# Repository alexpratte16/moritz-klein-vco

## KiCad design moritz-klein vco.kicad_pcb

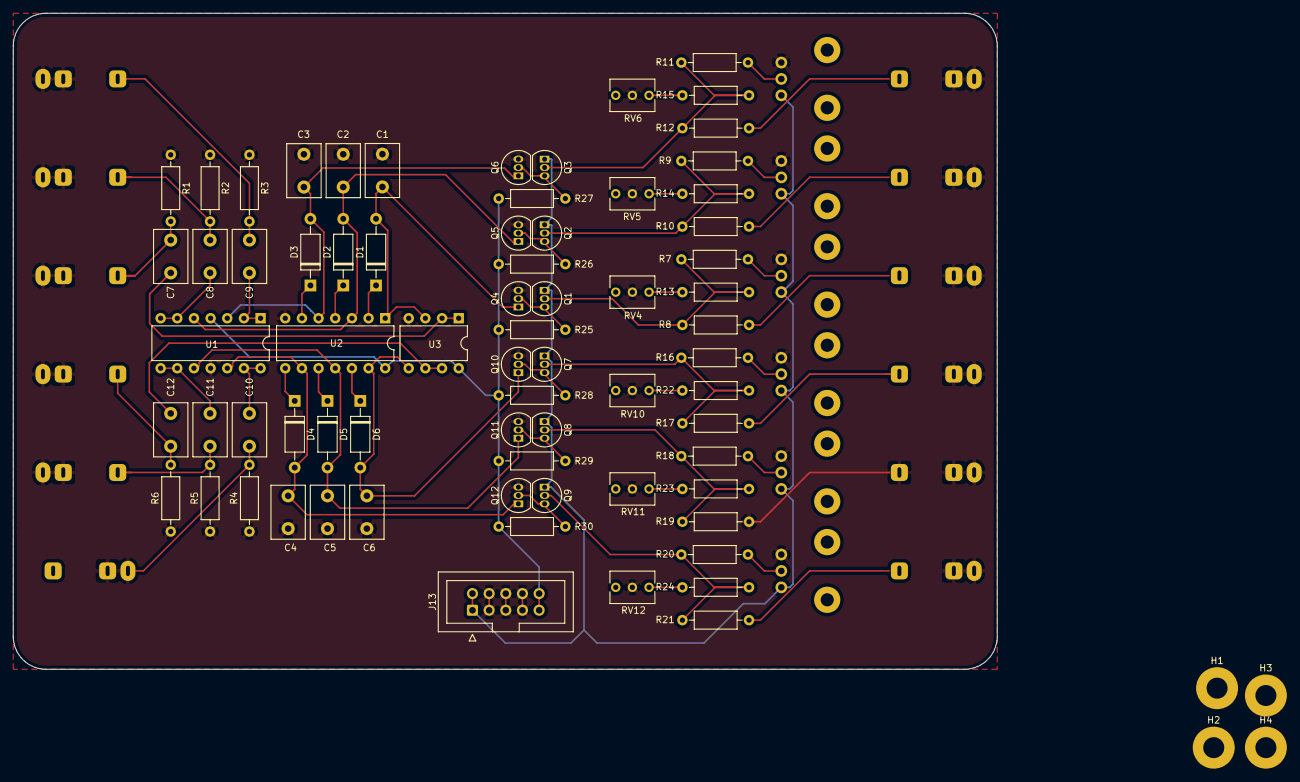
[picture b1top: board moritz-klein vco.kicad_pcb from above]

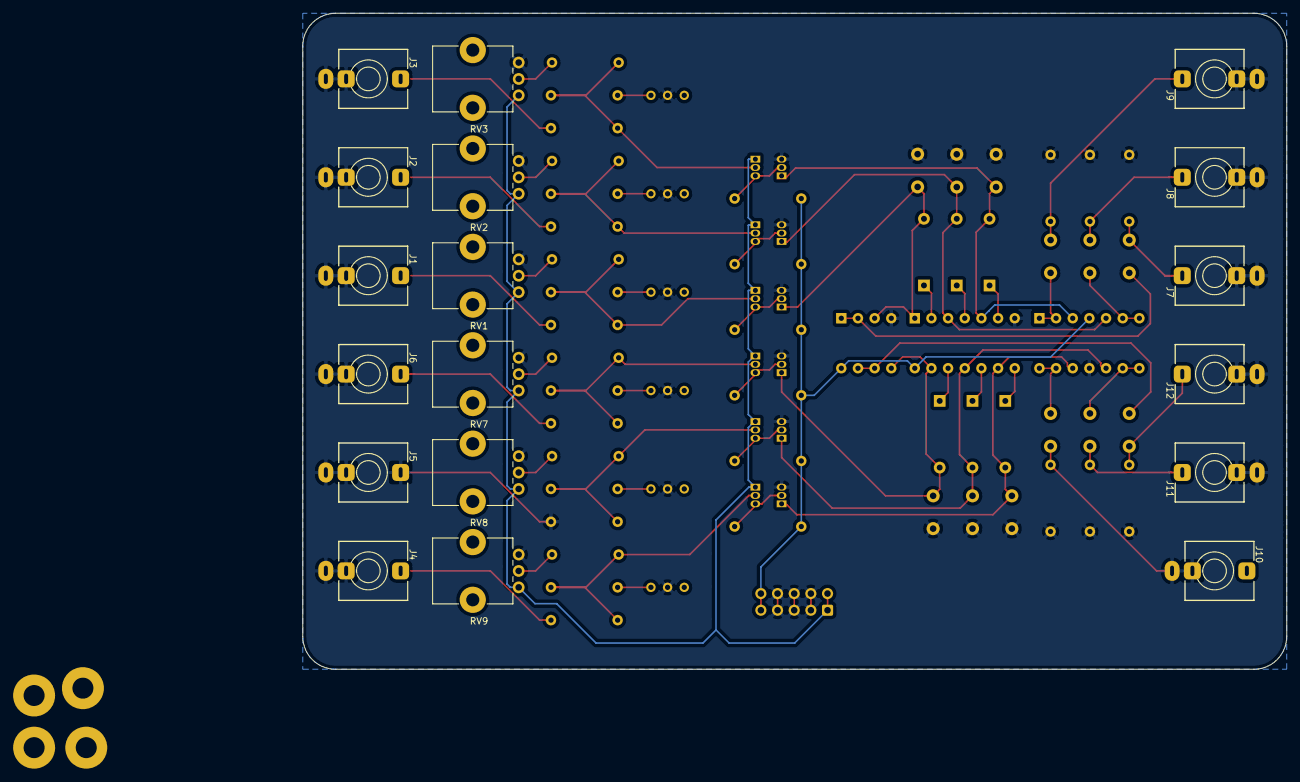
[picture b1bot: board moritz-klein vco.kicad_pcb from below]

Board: 2 copper layers, 150.0 x 100.0 mm, 92 parts (18 on the bottom side), 56 nets.

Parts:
C1, C2, C3, C4, C5, C6, C7, C8, C9, C10, C11, C12: C; C_Disc_D8.0mm_W5.0mm_P5.00mm
D1, D2, D3, D4, D5, D6: DIODE; D_A-405_P10.16mm_Horizontal
H1, H2, H3, H4: MountingHole; MountingHole_3.2mm_M3_Pad
J1, J2, J3, J4, J5, J6, J7, J8, J9, J10, J11, J12: AudioJack2_SwitchT; Jack_3.5mm_QingPu_WQP-PJ398SM_Vertical
J13: Conn_02x05_Odd_Even; IDC-Header_2x05_P2.54mm_Vertical
Q1, Q2, Q3, Q7, Q8, Q9: BC558; TO-92_Inline
Q4, Q5, Q6, Q10, Q11, Q12: BC548; TO-92_Inline
R1, R2, R3, R4, R5, R6, R7, R8, R9, R10, R11, R12, R16, R17, R18, R19, R20, R21: 100k; R_Axial_DIN0207_L6.3mm_D2.5mm_P10.16mm_Horizontal
R13, R14, R15, R22, R23, R24: 1.5k; R_Axial_DIN0207_L6.3mm_D2.5mm_P10.16mm_Horizontal
R25, R26, R27, R28, R29, R30: 1M; R_Axial_DIN0207_L6.3mm_D2.5mm_P10.16mm_Horizontal
RV1, RV2, RV3, RV7, RV8, RV9: R_POT; Potentiometer_Alps_RK09K_Single_Vertical
RV4, RV5, RV6, RV10, RV11, RV12: 1k; Potentiometer_Vishay_T73XW_Horizontal
U1: TL074; DIP-14_W7.62mm
U2: 40106; DIP-14_W7.62mm
U3: TL072; DIP-8_W7.62mm

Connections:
/cv_combined_a: Q1.2, R7.2, R8.1, R13.2
/cv_combined_b: Q2.2, R9.2, R10.1, R14.2
/cv_combined_c: Q3.2, R11.2, R12.1, R15.2
/cv_combined_d: Q9.2, R20.2, R21.1, R24.2
/cv_combined_e: Q8.2, R18.2, R19.1, R23.2
/cv_combined_f: Q7.2, R16.2, R17.1, R22.2
/cv_in_a: J1.T, R8.2
/cv_in_b: J2.T, R10.2
/cv_in_c: J3.T, R12.2
/cv_in_d: J4.T, R21.2
/cv_in_f: J6.T, R17.2
/saw_a: C7.1, U3.1, U3.2
/saw_b: C8.1, U1.6, U1.7
/saw_c: U1.1, U1.2
/saw_d: U1.13, U1.14
/saw_e: C11.1, U1.8, U1.9
/saw_f: C12.1, U3.6, U3.7
/schmidt_in_a: C1.1, D1.2, Q4.1, U2.1, U3.3
/schmidt_in_b: C2.1, D2.2, Q5.1, U1.5, U2.3
/schmidt_in_c: C3.1, D3.2, Q6.1, U1.3, U2.5
/schmidt_in_d: C4.1, D4.2, Q12.1, U1.12, U2.9
/schmidt_in_e: C5.1, D5.2, Q11.1, U1.10, U2.11
/schmidt_in_f: C6.1, D6.2, Q10.1, U2.13, U3.5
GND: C1.2, C2.2, C3.2, C4.2, C5.2, C6.2, J1.S, J1.TN, J2.S, J2.TN, J3.S, J3.TN, J4.S, J4.TN, J5.S, J5.T, J5.TN, J6.S, J6.TN, J7.S, J7.TN, J8.S, J8.TN, J9.S, J9.TN, J10.S, J10.TN, J11.S, J11.TN, J12.S, J12.TN, J13.3, J13.4, J13.5, J13.6, J13.7, J13.8, Q4.3, Q5.3, Q6.3, Q10.3, Q11.3, Q12.3, R1.1, R2.1, R3.1, R4.1, R5.1, R6.1, R19.2, RV1.1, RV2.1, RV3.1, RV4.2, RV5.2, RV6.2, RV7.1, RV8.1, RV9.1, RV10.2, RV11.2, RV12.2, U1.11, U2.7, U3.4
unnamed: C7.2, J7.T, R1.2
unnamed: C8.2, J8.T, R2.2
unnamed: C9.2, J9.T, R3.2
unnamed: C10.2, J10.T, R4.2
unnamed: C11.2, J11.T, R5.2
unnamed: C12.2, J12.T, R6.2
unnamed: D1.1, U2.2
unnamed: D2.1, U2.4
unnamed: D3.1, U2.6
unnamed: D4.1, U2.8
unnamed: D5.1, U2.10
unnamed: D6.1, U2.12
unnamed: Q1.3, Q4.2, R25.2
unnamed: Q2.3, Q5.2, R26.2
unnamed: Q3.3, Q6.2, R27.2
unnamed: Q7.3, Q10.2, R28.2
unnamed: Q8.3, Q11.2, R29.2
unnamed: Q9.3, Q12.2, R30.2
unnamed: R7.1, RV1.2
unnamed: R9.1, RV2.2
unnamed: R11.1, RV3.2
unnamed: R13.1, RV4.1
unnamed: R14.1, RV5.1
unnamed: R15.1, RV6.1
unnamed: R16.1, RV7.2
unnamed: R18.1, RV8.2
unnamed: R20.1, RV9.2
unnamed: R22.1, RV10.1
unnamed: R23.1, RV11.1
unnamed: R24.1, RV12.1
VCC: J13.9, J13.10, R25.1, R26.1, R27.1, R28.1, R29.1, R30.1, U1.4, U2.14, U3.8
VEE: J13.1, J13.2, Q1.1, Q2.1, Q3.1, Q7.1, Q8.1, Q9.1, RV1.3, RV2.3, RV3.3, RV7.3, RV8.3, RV9.3

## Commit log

2022-09-18 First commit, getting ready for manufacturing.
2022-09-18 Jack was on the wrong side of the pcb.
